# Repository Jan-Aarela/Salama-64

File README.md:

<!-- vim: ft=markdown nospell
-->
<i>

# Selkäsalama-64
Möykkäwaunujen proto salaman teon aikana huomasin, että salaman koko oli pikkasen pienempi mitä kuvittelin. Täysin toimiva siitähän tuli ja varsin hieno vaikka nopeasti tekasin sen.

Kaytin protoversiota yövalona kotona :D ja iski idea. Mitä jos, tästä tekisi selkäsalaman.  
[Niinkuin ysärillä...](https://github.com/Elektroniikkakerho/Archived-projects/tree/master/salama)  KiCadi tulille vaan ja lopputulos alla:

## Kuvia härpäkkeestä
|Homma in action|Etupuoli|Takapuoli| Takapuoli Kuorilla|
|---|---|---|---|
| | |  | 

## Skema
Homma toimii siten, että virtapankista tulee 5V ja menee suoraan piiriin. Konkka tasoittaa virran ja vastus toimii kuormana, mikäli virtapankki sammuu liian vähäistä virrankulutuksesta. Toinen ja energia tehokkaampi vaihtoehto on käyttää virtapankki kikkaa, eli ajoittain piikittää virran kulutusta ohjaamalla transistorin avulla vastusta.

Ledit on jaettu puolin kahteen eri charlieplexiin. (7^2-7 (-10) viritelmällä).  
Miksei kaikkia ledejä yhteen pleksiin? No siksi koska jos yhteen pleksiin laittaa kaikki ledit niin duty cycle olisi ~1.5%, joka on aika pieni. Kahdella pleksillä sen saa ~3%, jolloin ledit ovat kirkkaampia.

Napin tai liukukytkimen voi halutessa laittaa SW1 kohtaan johdoilla ja laittaa itse napin/liukukytkimen haalareihin, esim. kaulapantaan tai mikälie sen oikea nimi onkaan.

## Osaluettelo
| KPL | MITÄ               | HUOM    | 
|:---:|:---                |:---    |
|  1  | ATtiny 861A SOIC   |       Vähintään: Flash 4KB -  SRAM 256B   |
|  64 | 5mm DIP LED        | Tekijällä XL-502UBC ledit  |
|  14  | 27 Ohm 1206        |    < 20ma per IO pin    |
|  1  | 10 uF tant. 2312 SMD     |    Virtalähteen virran tasoitusta varten |
|  8  | Johdon pätkiä    |    Levyjen yhdistämiseen AWG 22-24 |
| 1 | Virtakaapelipari | Esim. USB |
| 1 | 6 pinninen rima | THT vaaka versio |

| Muuta?  |
|:---|
| Fläshäykseen Arduino ja 6 pinninen rima |
| PETG Filamettia kuorien tulostamiseen|
| (Optinal) Lisävastus mikäli salama sammuu|
| (Optinal) 2kpl 1206 100 nF keraamisia konkkia  |
| (Optinal) Nappi/Liukukytkin halutessa ja siihen johdot|

## Piirilevyt

Mikäli kerholla ei ole levyjä tähän projektiin, voit yrittää tehdä levyn esimerkiksi jyrsimällä tai etsaamalla. Tracien paksuudet ovat 0.4mm kestävyyden/tuotannon tolaranssin takia. Projektiin käy esimerkiksi 2-puoleinen 1oz 1.6mm PCB. Jos teet paksummasta levystä piirilevyt, joudut muokkaamaan kuorien mitat, jotta levyt mahtuvat niihin. 

Läpivientien kanssa joutuu painimaan sillä jyrsimisen/perus etsauksen jälkeen ne ei ilmesty itsestään vaan ne joutuu manuaalisesti tehdä ne. Yks tapa on käyttää läpivientiniittejä ja pressiä. Pressin jälkeen kannattaa ehdottamasti juottaa niitit traceihin, että varmasti toimivat. Jos niitit eivät mahdu reikiin, täytyy vaihtaa vioiden ja ledien reikien koot kicadillä. Tarkista, että niittien läpi mahtuu komponentit. Voi olla, että reikiä pitää kasvattaa...

## LEDIT
Tähän kannatta käyttää hyvin kirkkaita ledejä esim.  10000 mcd tai kirkkaammat,   
koska yhden ledin duty cycle on sen 1/32 ajasta eli ~ 3%.

Testaa ledin kirkkaus virtalähteellä.
Asetukset: square, 2.5V offset, 2.5V amplitude ja 3% duty cycle.

**Jos ledejä ei ole diffusoitu, niin ehdottamasti diffusoi ne.**  
Muuten selkäsalamasta tulee saatananmoinen valokeila ja sivusta katsottuna näyttää himmeältä.  

Hidas, mutta puhtaamman jäljen saat kun hiot jokaisen ledin 400-600 grid vesihiomapaperilla.

Toinen ja huomattavasti nopeampi tapa on käyttää hiekkapuhallinta. 
Eli laita kaikki ledit reikälevyyn ja teippaa ledien jalat.
Samaan tyliin kuin konkat tulee rullana. Ja ei muutakun hiekkapuhaltimella ammuskelemaan.
Voit puhdistaa ledit hiekasta laittamalla ledit astiaan jossa on nestettä (vesi/ipa) ja astian ultraäänipuhdistimeen.

## Kasausohjeet
Projekti aika pitkälti noudattaa possusalaman ohjeita.

 1. Juota siis piiri, konkka, 14 vastusta ja piikkirima.  
    Piikkirimasta trimmataan 4 sisimmäistä jalkaa, että se asettuisi lättänä.

2. Seuraavaksi laitetaan piirilevyt kiinni haalareihin.  
    Katko ledien jalat teräviksi ja yritä kohdistaa levy paikalleen.  
    Tässä kannattaa laittaa ledit niin, että haalarin salaman ääriviivat kulkee ledien keskellä.  
    Ledit mahdollisman hyvin kiinni piirilevyä vasten, näyttää suoremmalta.  
    Ja kannattaa jättää pieni rako piirilevyjen välille,  ettei hankaudu.  
    Tee sama toiselle piirilevylle. 

3. Sitten voit juottaa hyppyjohdot levylle, jossa on piiri.  
    Kannattaa juottaa hyvin ja niin että johdon muovi on mahdollisimman lähellä levyä.  
    Katko juottamisen jälkeen etupuolelta töpröttävät johdot pätkät.

4. Sittenkun kummatkin levyt ovat haalareissa kiinni, yhdistä levyt hyppykaapelilla.  
    Kaapelit menee järjestyksessä. Kanattaa olla vähän löysää, että koko härpäke pystyy taittumaan.

5. Kiinnitä Ardu piikkirimaan kiinni ja siirrä koodi levylle käyttäen AVR-ISP.  
    Ohjeet alempana.

6.  Jos kaikki toimii, juota seuraavaksi virtakaapeli ja tarvittaessa kuormavastus mikäli virtapankki lopettaa virranannon (virtasyöppö esto). Esim. 110 Ohm tai 169 Ohm...

7. Kuoret saa tulostettua FabLabilla ja mielellään kannattaa käyttää PETG. Tämä taipuu hyvin eikä halkea yhtä herkästi verrattuna esim. ABS muoviin. Tulostuksen jälkeen pitää putsata kuorien klipsien/kielien supportit pois. Esim varovasti veitsellä. Voit testata, että mahtuuko levy siihen, jos laitat 1.6mm levyn pätkän klipsin ja reunan (jossa piirilevyt istuu) väliin.

    Jos olet tehnyt piirilevyt paksummasta levystä, pitää muokata kuorien mittoja joko muokkaamalla STL tai blender projekti tiedostoa. 

8. Kuoret sopivat kummallekin piirilevylle.  
    Kolvilla voit tehdä master levyn kuoren reunalle reiän virtakaapelille.

    Kannattaa laittaa kuoret kiinni siten, että laitat ensin terävän kulman ensin kiinni ja siitä sitten siirry ylöspäin. Venytä kuorta ulospäin paina kiinni.

    Juuh, eikait siinä. Nyt **JÖÖTI** "possu" selässä  👌

## Koodi

```bash
# Siirry koodi kansioon
cd src/

# Koodin kääntäminen
avr-gcc -mmcu=attiny861 main.c kuviot.c vilkutus_charlie.c -I./ -Os -ffunction-sections -fdata-sections -Wl,--gc-sections -DF_CPU=8000000U

# Fuse asetukset
avrdude -c avrisp -p t861 -P /dev/ttyUSB0 -b 19200 -U lfuse:w:0xe2:m -U hfuse:w:0xdf:m

# Koodin siirto levylle
avrdude -c avrisp -p t861 -P /dev/ttyUSB0 -b 19200 -U flash:w:a.out

# Testaukseen voit käyttää yhtä komento riviä yhdistämällä koodin käännös ja siirto komennot (bash:)
avr-gcc -mmcu=attiny861 main.c kuviot.c vilkutus_charlie.c -I./ -Os -ffunction-sections -fdata-sections -Wl,--gc-sections -DF_CPU=8000000U && sudo avrdude -c avrisp -p t861 -P /dev/ttyUSB0 -b 19200 -U flash:w:a.out
```

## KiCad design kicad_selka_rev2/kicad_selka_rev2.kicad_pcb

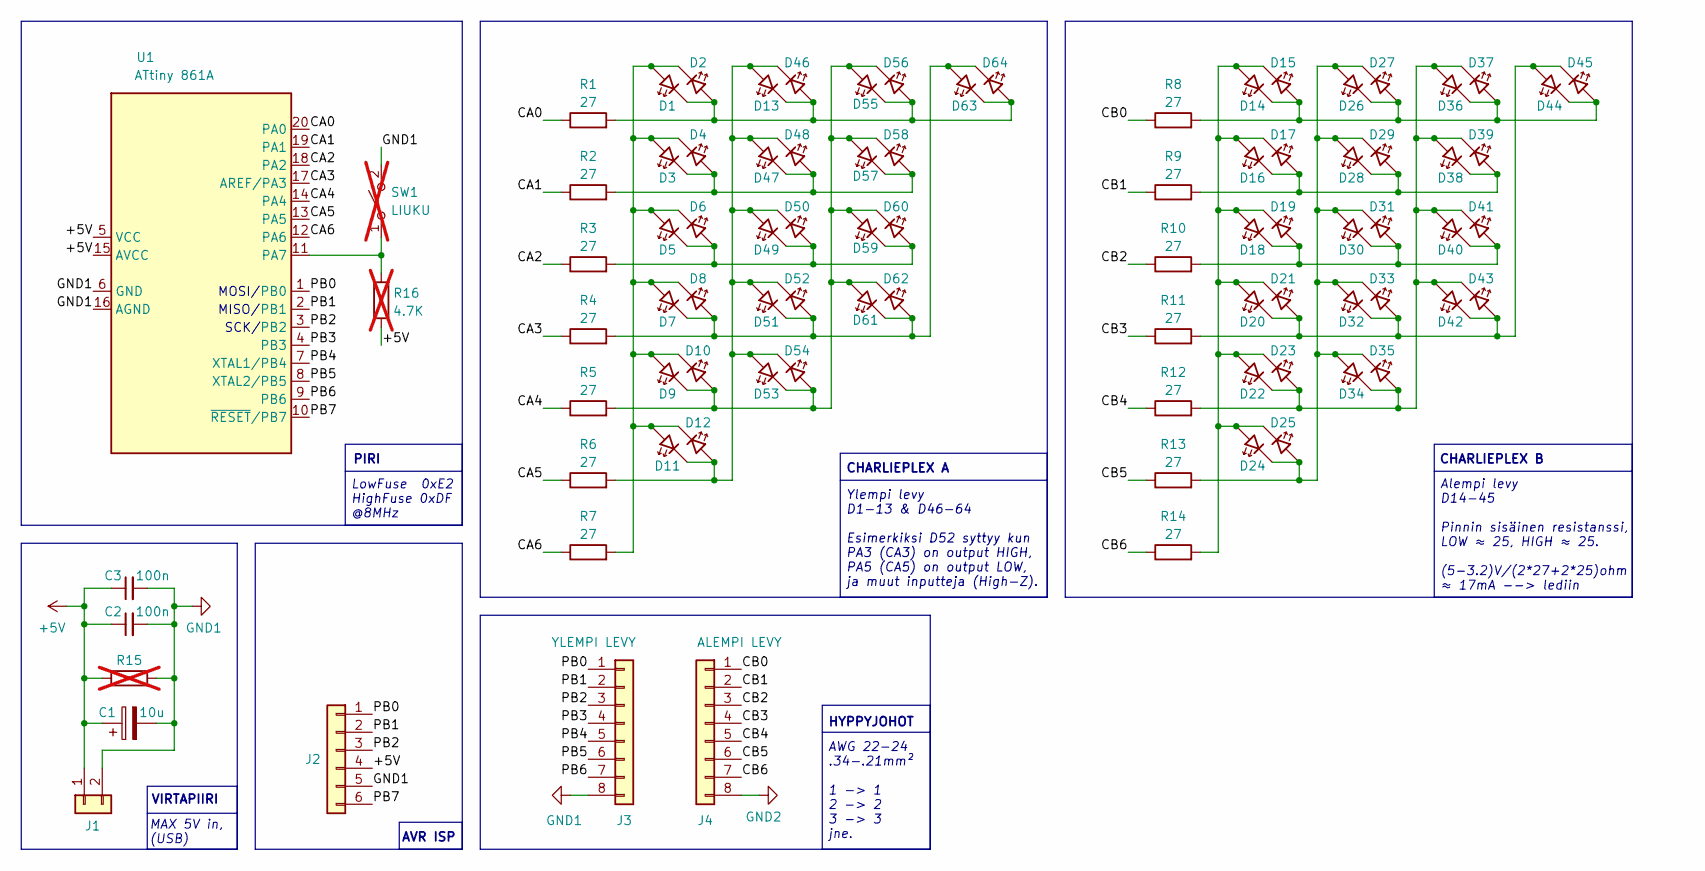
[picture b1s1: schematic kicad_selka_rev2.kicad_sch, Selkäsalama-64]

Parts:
C1: 10u; CP_EIA-6032-28_Kemet-C_HandSolder
C2, C3: 100n; C_1206_3216Metric_Pad1.33x1.80mm_HandSolder
D1, D2, D3, D4, D5, D6, D7, D8, D9, D10, D11, D12, D13, D14, D15, D16, D17, D18, D19, D20, D21, D22, D23, D24, D25, D26, D27, D28, D29, D30, D31, D32, D33, D34, D35, D36, D37, D38, D39, D40, D41, D42, D43, D44, D45, D46, D47, D48, D49, D50, D51, D52, D53, D54, D55, D56, D57, D58, D59, D60, D61, D62, D63, D64: LED_45deg; LED_D5.0mm_blue_zani
J1: Conn_01x02; PinHeader_1x02_P2.54mm_Vertical
J2: Conn_01x06; PinHeader_1x06_P2.54mm_Horizontal_smd_tht
J3, J4: Conn_01x08; PinHeader_1x08_P2.00mm_Vertical_levee
R1, R2, R3, R4, R5, R6, R7, R8, R9, R10, R11, R12, R13, R14: 27; R_1206_3216Metric_Pad1.30x1.75mm_HandSolder
R15: X; R_1210_3225Metric_Pad1.30x2.65mm_HandSolder; not fitted
R16: 4.7K; R_0805_2012Metric_Pad1.20x1.40mm_HandSolder; not fitted
SW1: LIUKU; PinHeader_1x02_P2.54mm_Vertical; not fitted
U1: ATtiny 861A; SOIC-20W_7.5x12.8mm_P1.27mm

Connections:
+5V: C1.1, C2.1, C3.1, J1.1, J2.4, R15.1, R16.1, U1.5 (VCC), U1.15 (AVCC)
/CA0: R1.1, U1.20 (PA0)
/CA1: R2.1, U1.19 (PA1)
/CA2: R3.1, U1.18 (PA2)
/CA3: R4.1, U1.17 (AREF/PA3)
/CA4: R5.1, U1.14 (PA4)
/CA5: R6.1, U1.13 (PA5)
/CA6: R7.1, U1.12 (PA6)
/CB0: J4.1, R8.1
/CB1: J4.2, R9.1
/CB2: J4.3, R10.1
/CB3: J4.4, R11.1
/CB4: J4.5, R12.1
/CB5: J4.6, R13.1
/CB6: J4.7, R14.1
/PB0: J2.1, J3.1, U1.1 (PB0)
/PB1: J2.2, J3.2, U1.2 (PB1)
/PB2: J2.3, J3.3, U1.3 (PB2)
/PB3: J3.4, U1.4 (PB3)
/PB4: J3.5, U1.7 (XTAL1/PB4)
/PB5: J3.6, U1.8 (XTAL2/PB5)
/PB6: J3.7, U1.9 (PB6)
/PB7: J2.6, U1.10 (~RESET/PB7)
GND1: C1.2, C2.2, C3.2, J1.2, J2.5, J3.8, R15.2, SW1.2 (B), U1.6 (GND), U1.16 (AGND)
GND2: J4.8
unnamed: D1.2 (A), D2.1 (K), D3.2 (A), D4.1 (K), D5.2 (A), D6.1 (K), D7.2 (A), D8.1 (K), D9.2 (A), D10.1 (K), D11.2 (A), D12.1 (K), R7.2
unnamed: D1.1 (K), D2.2 (A), D13.1 (K), D46.2 (A), D55.1 (K), D56.2 (A), D63.1 (K), D64.2 (A), R1.2
unnamed: D3.1 (K), D4.2 (A), D47.1 (K), D48.2 (A), D57.1 (K), D58.2 (A), R2.2
unnamed: D9.1 (K), D10.2 (A), D53.1 (K), D54.2 (A), D55.2 (A), D56.1 (K), D57.2 (A), D58.1 (K), D59.2 (A), D60.1 (K), D61.2 (A), D62.1 (K), R5.2
unnamed: D11.1 (K), D12.2 (A), D13.2 (A), D46.1 (K), D47.2 (A), D48.1 (K), D49.2 (A), D50.1 (K), D51.2 (A), D52.1 (K), D53.2 (A), D54.1 (K), R6.2
unnamed: D14.2 (A), D15.1 (K), D16.2 (A), D17.1 (K), D18.2 (A), D19.1 (K), D20.2 (A), D21.1 (K), D22.2 (A), D23.1 (K), D24.2 (A), D25.1 (K), R14.2
unnamed: D14.1 (K), D15.2 (A), D26.1 (K), D27.2 (A), D36.1 (K), D37.2 (A), D44.1 (K), D45.2 (A), R8.2
unnamed: D16.1 (K), D17.2 (A), D28.1 (K), D29.2 (A), D38.1 (K), D39.2 (A), R9.2
unnamed: D18.1 (K), D19.2 (A), D30.1 (K), D31.2 (A), D40.1 (K), D41.2 (A), R10.2
unnamed: D20.1 (K), D21.2 (A), D32.1 (K), D33.2 (A), D42.1 (K), D43.2 (A), D44.2 (A), D45.1 (K), R11.2
unnamed: D22.1 (K), D23.2 (A), D34.1 (K), D35.2 (A), D36.2 (A), D37.1 (K), D38.2 (A), D39.1 (K), D40.2 (A), D41.1 (K), D42.2 (A), D43.1 (K), R12.2
unnamed: D24.1 (K), D25.2 (A), D26.2 (A), D27.1 (K), D28.2 (A), D29.1 (K), D30.2 (A), D31.1 (K), D32.2 (A), D33.1 (K), D34.2 (A), D35.1 (K), R13.2
unnamed: D5.1 (K), D6.2 (A), D49.1 (K), D50.2 (A), D59.1 (K), D60.2 (A), R3.2
unnamed: D7.1 (K), D8.2 (A), D51.1 (K), D52.2 (A), D61.1 (K), D62.2 (A), D63.2 (A), D64.1 (K), R4.2
unnamed: R16.2, SW1.1 (A), U1.11 (PA7)

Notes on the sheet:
VIRTAPIIRI
SCK/
MISO/
MOSI/
AWG 22-24 .34-.21mm² 1 -> 1 2 -> 2 3 -> 3 jne.
CHARLIEPLEX A
CHARLIEPLEX B
MAX 5V in, (USB)
Ylempi levy D1-13 & D46-64 Esimerkiksi D52 syttyy kun PA3 (CA3) on output HIGH, PA5 (CA5) on output LOW, ja muut inputteja (High-Z).
Alempi levy D14-45 Pinnin sisäinen resistanssi, LOW ≈ 25, HIGH ≈ 25. (5-3.2)V/(2*27+2*25)ohm ≈ 17mA --> lediin
AVR ISP
PIRI
LowFuse 0xE2 HighFuse 0xDF @8MHz
HYPPYJOHOT

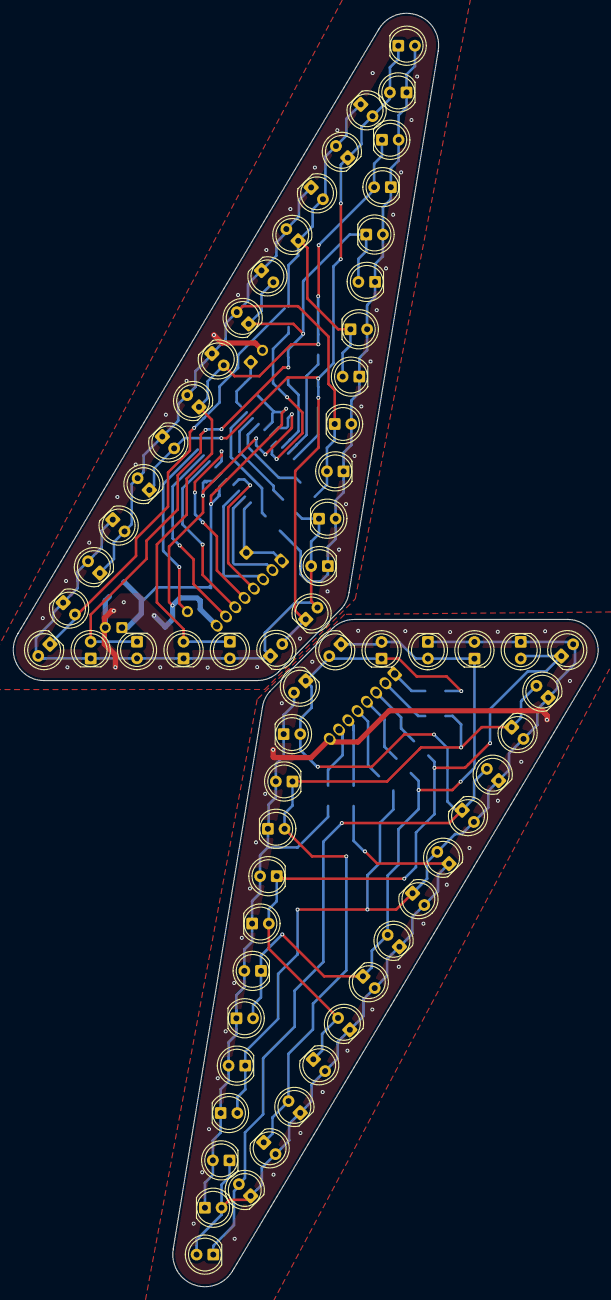
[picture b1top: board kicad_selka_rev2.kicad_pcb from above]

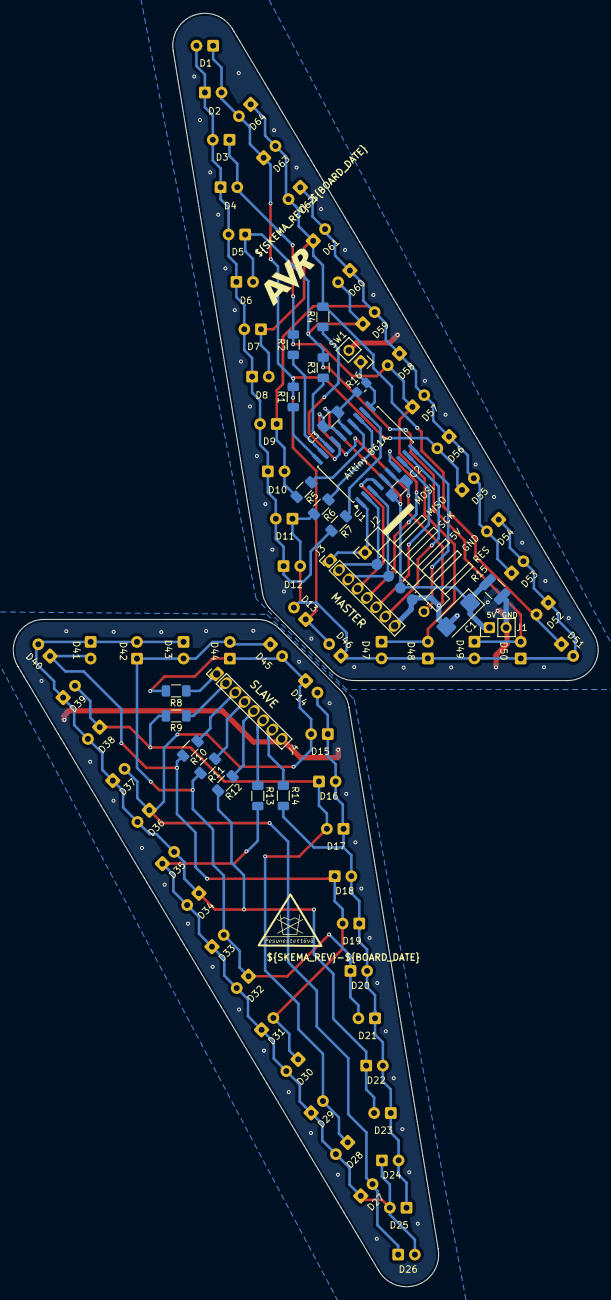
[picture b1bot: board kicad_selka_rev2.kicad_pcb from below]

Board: 2 copper layers, 89.2 x 194.1 mm, 89 parts (25 on the bottom side), 39 nets.

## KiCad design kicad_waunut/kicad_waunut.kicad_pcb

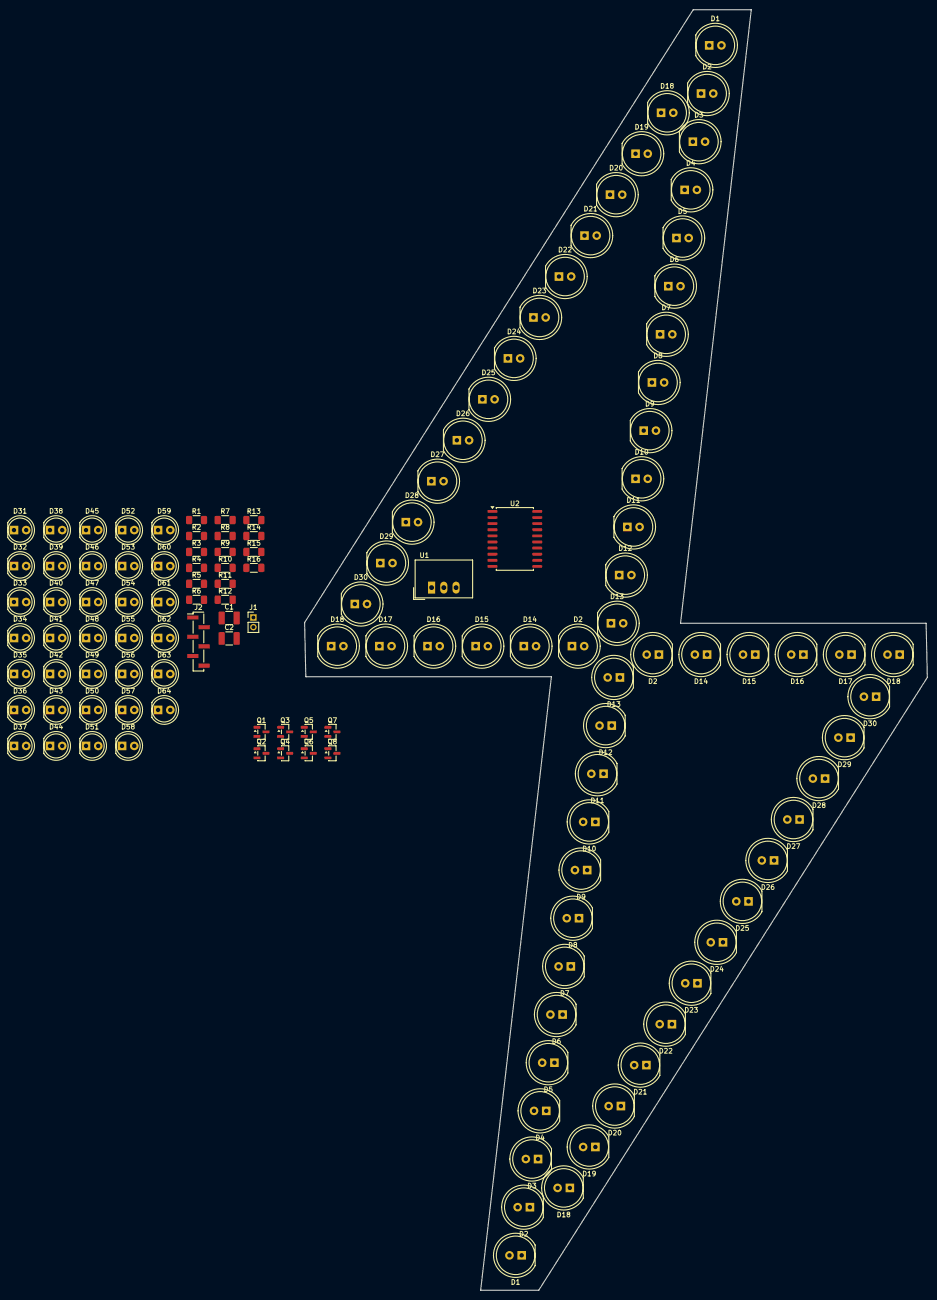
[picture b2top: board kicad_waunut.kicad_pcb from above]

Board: 2 copper layers, 129.3 x 265.9 mm, 128 parts (0 on the bottom side), 43 nets, no tracks yet.

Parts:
C1, C2: 10 u; C_1210_3225Metric_Pad1.33x2.70mm_HandSolder
D1, D1#2, D2, D2#2, D2#3, D2#4, D3, D3#2, D4, D4#2, D5, D5#2, D6, D6#2, D7, D7#2, D8, D8#2, D9, D9#2, D10, D10#2, D11, D11#2, D12, D12#2, D13, D13#2, D14, D14#2, D15, D15#2, D16, D16#2, D17, D17#2, D18, D18#2, D18#3, D18#4, D19, D19#2, D20, D20#2, D21, D21#2, D22, D22#2, D23, D23#2, D24, D24#2, D25, D25#2, D26, D26#2, D27, D27#2, D28, D28#2, D29, D29#2, D30, D30#2: LED; LED_D8.0mm
D31, D32, D33, D34, D35, D36, D37, D38, D39, D40, D41, D42, D43, D44, D45, D46, D47, D48, D49, D50, D51, D52, D53, D54, D55, D56, D57, D58, D59, D60, D61, D62, D63, D64: LED; LED_D5.0mm
J1: Conn_01x02_Pin; PinHeader_1x02_P2.00mm_Vertical
J2: Conn_01x06_Pin; PinHeader_1x06_P2.00mm_Vertical_SMD_Pin1Left
Q1, Q2, Q3, Q4, Q5, Q6, Q7, Q8: NPN; SOT-23
R1, R2, R3, R4, R5, R6, R7, R8: 110; R_1206_3216Metric_Pad1.30x1.75mm_HandSolder
R9, R10, R11, R12, R13, R14, R15, R16: 1000; R_1206_3216Metric_Pad1.30x1.75mm_HandSolder
U1: TSR1-2450E; Converter_DCDC_TRACO_TSR-1_THT
U2: ATtiny861A-S; SOIC-20W_7.5x12.8mm_P1.27mm

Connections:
+5V: C1.1, J2.4, U1.3 (Vout), U2.5 (VCC), U2.15 (AVCC)
+12V: C2.1, J1.1, U1.1 (Vin)
GND: C1.2, C2.2, J1.2, J2.5, Q1.3 (E), Q2.3 (E), Q3.3 (E), Q4.3 (E), Q5.3 (E), Q6.3 (E), Q7.3 (E), Q8.3 (E), U1.2 (GND), U2.6 (GND), U2.16 (AGND)
unnamed: D1.2 (A), D1#2.2 (A), D9.2 (A), D9#2.2 (A), D17.2 (A), D17#2.2 (A), D25.2 (A), D25#2.2 (A), D33.2 (A), D41.2 (A), D49.2 (A), D57.2 (A), R1.2
unnamed: D1.1 (K), D1#2.1 (K), D2.1 (K), D2#2.1 (K), D2#3.1 (K), D2#4.1 (K), D3.1 (K), D3#2.1 (K), D4.1 (K), D4#2.1 (K), D5.1 (K), D5#2.1 (K), D6.1 (K), D6#2.1 (K), D7.1 (K), D7#2.1 (K), D8.1 (K), D8#2.1 (K), Q1.1 (C)
unnamed: D2.2 (A), D2#2.2 (A), D2#3.2 (A), D2#4.2 (A), D10.2 (A), D10#2.2 (A), D18.2 (A), D18#2.2 (A), D18#3.2 (A), D18#4.2 (A), D26.2 (A), D26#2.2 (A), D34.2 (A), D42.2 (A), D50.2 (A), D58.2 (A), R2.2
unnamed: D9.1 (K), D9#2.1 (K), D10.1 (K), D10#2.1 (K), D11.1 (K), D11#2.1 (K), D12.1 (K), D12#2.1 (K), D13.1 (K), D13#2.1 (K), D14.1 (K), D14#2.1 (K), D15.1 (K), D15#2.1 (K), D16.1 (K), D16#2.1 (K), Q2.1 (C)
unnamed: D3.2 (A), D3#2.2 (A), D11.2 (A), D11#2.2 (A), D19.2 (A), D19#2.2 (A), D27.2 (A), D27#2.2 (A), D35.2 (A), D43.2 (A), D51.2 (A), D59.2 (A), R3.2
unnamed: D4.2 (A), D4#2.2 (A), D12.2 (A), D12#2.2 (A), D20.2 (A), D20#2.2 (A), D28.2 (A), D28#2.2 (A), D36.2 (A), D44.2 (A), D52.2 (A), D60.2 (A), R4.2
unnamed: D5.2 (A), D5#2.2 (A), D13.2 (A), D13#2.2 (A), D21.2 (A), D21#2.2 (A), D29.2 (A), D29#2.2 (A), D37.2 (A), D45.2 (A), D53.2 (A), D61.2 (A), R5.2
unnamed: D6.2 (A), D6#2.2 (A), D14.2 (A), D14#2.2 (A), D22.2 (A), D22#2.2 (A), D30.2 (A), D30#2.2 (A), D38.2 (A), D46.2 (A), D54.2 (A), D62.2 (A), R6.2
unnamed: D7.2 (A), D7#2.2 (A), D15.2 (A), D15#2.2 (A), D23.2 (A), D23#2.2 (A), D31.2 (A), D39.2 (A), D47.2 (A), D55.2 (A), D63.2 (A), R7.2
unnamed: D8.2 (A), D8#2.2 (A), D16.2 (A), D16#2.2 (A), D24.2 (A), D24#2.2 (A), D32.2 (A), D40.2 (A), D48.2 (A), D56.2 (A), D64.2 (A), R8.2
unnamed: D17.1 (K), D17#2.1 (K), D18.1 (K), D18#2.1 (K), D18#3.1 (K), D18#4.1 (K), D19.1 (K), D19#2.1 (K), D20.1 (K), D20#2.1 (K), D21.1 (K), D21#2.1 (K), D22.1 (K), D22#2.1 (K), D23.1 (K), D23#2.1 (K), D24.1 (K), D24#2.1 (K), Q3.1 (C)
unnamed: D25.1 (K), D25#2.1 (K), D26.1 (K), D26#2.1 (K), D27.1 (K), D27#2.1 (K), D28.1 (K), D28#2.1 (K), D29.1 (K), D29#2.1 (K), D30.1 (K), D30#2.1 (K), D31.1 (K), D32.1 (K), Q4.1 (C)
unnamed: D33.1 (K), D34.1 (K), D35.1 (K), D36.1 (K), D37.1 (K), D38.1 (K), D39.1 (K), D40.1 (K), Q5.1 (C)
unnamed: D41.1 (K), D42.1 (K), D43.1 (K), D44.1 (K), D45.1 (K), D46.1 (K), D47.1 (K), D48.1 (K), Q6.1 (C)
unnamed: D49.1 (K), D50.1 (K), D51.1 (K), D52.1 (K), D53.1 (K), D54.1 (K), D55.1 (K), D56.1 (K), Q7.1 (C)
unnamed: D57.1 (K), D58.1 (K), D59.1 (K), D60.1 (K), D61.1 (K), D62.1 (K), D63.1 (K), D64.1 (K), Q8.1 (C)
unnamed: J2.1, R9.1, U2.1 (PB0)
unnamed: J2.2, R10.1, U2.2 (PB1)
unnamed: J2.3, R11.1, U2.3 (PB2)
unnamed: J2.6, R16.1, U2.10 (~RESET/PB7)
unnamed: Q1.2 (B), R9.2
unnamed: Q2.2 (B), R10.2
unnamed: Q3.2 (B), R11.2
unnamed: Q4.2 (B), R12.2
unnamed: Q5.2 (B), R13.2
unnamed: Q6.2 (B), R14.2
unnamed: Q7.2 (B), R15.2
unnamed: Q8.2 (B), R16.2
unnamed: R4.1, U2.17 (AREF/PA3)
unnamed: R1.1, U2.20 (PA0)
unnamed: R2.1, U2.19 (PA1)
unnamed: R3.1, U2.18 (PA2)
unnamed: R5.1, U2.14 (PA4)
unnamed: R6.1, U2.13 (PA5)
unnamed: R7.1, U2.12 (PA6)
unnamed: R8.1, U2.11 (PA7)
unnamed: R12.1, U2.4 (PB3)
unnamed: R15.1, U2.9 (PB6)
unnamed: R13.1, U2.7 (XTAL1/PB4)
unnamed: R14.1, U2.8 (XTAL2/PB5)

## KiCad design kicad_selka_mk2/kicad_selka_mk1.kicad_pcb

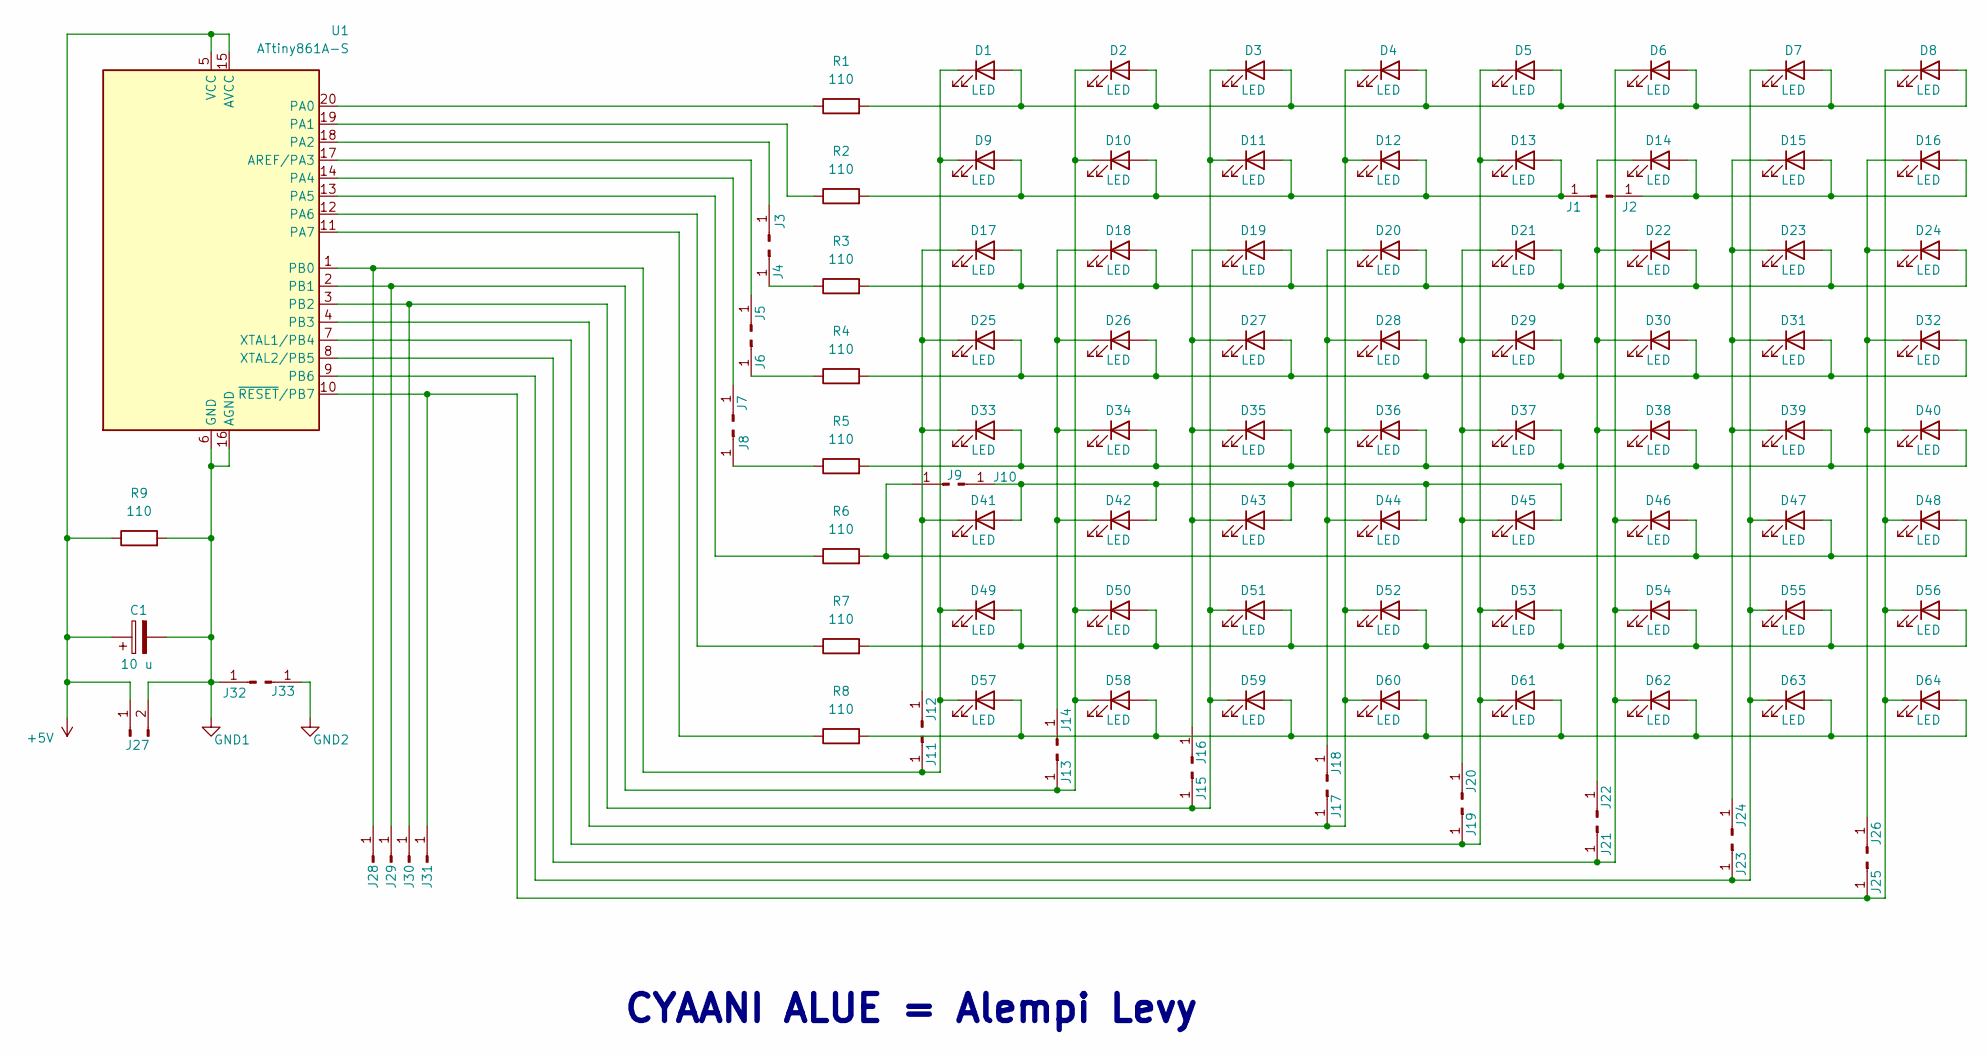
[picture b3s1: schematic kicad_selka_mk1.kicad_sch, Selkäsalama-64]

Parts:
C1: 10 u; C_1210_3225Metric_Pad1.33x2.70mm_HandSolder
D1, D2, D3, D4, D5, D6, D7, D8, D9, D10, D11, D12, D13, D14, D15, D16, D17, D18, D19, D20, D21, D22, D23, D24, D25, D26, D27, D28, D29, D30, D31, D32, D33, D34, D35, D36, D37, D38, D39, D40, D41, D42, D43, D44, D45, D46, D47, D48, D49, D50, D51, D52, D53, D54, D55, D56, D57, D58, D59, D60, D61, D62, D63, D64: LED; LED_D5.0mm
J1, J2, J3, J5, J6, J7, J8, J9, J10, J11, J12, J13, J14, J15, J16, J17, J18, J19, J20, J21, J22, J23, J24, J25, J26, J32, J33: Conn_01x01_Pin; PinSocket_1x01_P2.54mm_Vertical
J4: Conn_01x01_Pin; Pin_D0.7mm_L6.5mm_W1.8mm_FlatFork
J27: Conn_01x02_Pin; PinHeader_1x02_P2.00mm_Vertical
J28, J29, J30, J31: Conn_01x01_Pin; TestPoint_Pad_1.0x1.0mm
R1, R2, R3, R4, R5, R6, R7, R8, R9: 110; R_1206_3216Metric_Pad1.30x1.75mm_HandSolder
U1: ATtiny861A-S; SOIC-20W_7.5x12.8mm_P1.27mm

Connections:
+5V: C1.1, J27.1, R9.1, U1.5 (VCC), U1.15 (AVCC)
GND1: C1.2, J27.2, J32.1, R9.2, U1.6 (GND), U1.16 (AGND)
GND2: J33.1
unnamed: D1.2 (A), D2.2 (A), D3.2 (A), D4.2 (A), D5.2 (A), D6.2 (A), D7.2 (A), D8.2 (A), R1.2
unnamed: D1.1 (K), D9.1 (K), D49.1 (K), D57.1 (K), J11.1, J28.1, U1.1 (PB0)
unnamed: D9.2 (A), D10.2 (A), D11.2 (A), D12.2 (A), D13.2 (A), J1.1, R2.2
unnamed: D2.1 (K), D10.1 (K), D50.1 (K), D58.1 (K), J13.1, J29.1, U1.2 (PB1)
unnamed: D3.1 (K), D11.1 (K), D51.1 (K), D59.1 (K), J15.1, J30.1, U1.3 (PB2)
unnamed: D4.1 (K), D12.1 (K), D52.1 (K), D60.1 (K), J17.1, U1.4 (PB3)
unnamed: D5.1 (K), D13.1 (K), D53.1 (K), D61.1 (K), J19.1, U1.7 (XTAL1/PB4)
unnamed: D14.2 (A), D15.2 (A), D16.2 (A), J2.1
unnamed: D14.1 (K), D22.1 (K), D30.1 (K), D38.1 (K), J22.1
unnamed: D15.1 (K), D23.1 (K), D31.1 (K), D39.1 (K), J24.1
unnamed: D16.1 (K), D24.1 (K), D32.1 (K), D40.1 (K), J26.1
unnamed: D17.2 (A), D18.2 (A), D19.2 (A), D20.2 (A), D21.2 (A), D22.2 (A), D23.2 (A), D24.2 (A), R3.2
unnamed: D17.1 (K), D25.1 (K), D33.1 (K), D41.1 (K), J12.1
unnamed: D18.1 (K), D26.1 (K), D34.1 (K), D42.1 (K), J14.1
unnamed: D19.1 (K), D27.1 (K), D35.1 (K), D43.1 (K), J16.1
unnamed: D20.1 (K), D28.1 (K), D36.1 (K), D44.1 (K), J18.1
unnamed: D21.1 (K), D29.1 (K), D37.1 (K), D45.1 (K), J20.1
unnamed: D25.2 (A), D26.2 (A), D27.2 (A), D28.2 (A), D29.2 (A), D30.2 (A), D31.2 (A), D32.2 (A), R4.2
unnamed: D33.2 (A), D34.2 (A), D35.2 (A), D36.2 (A), D37.2 (A), D38.2 (A), D39.2 (A), D40.2 (A), R5.2
unnamed: D41.2 (A), D42.2 (A), D43.2 (A), D44.2 (A), D45.2 (A), J10.1
unnamed: D46.2 (A), D47.2 (A), D48.2 (A), J9.1, R6.2
unnamed: D6.1 (K), D46.1 (K), D54.1 (K), D62.1 (K), J21.1, U1.8 (XTAL2/PB5)
unnamed: D7.1 (K), D47.1 (K), D55.1 (K), D63.1 (K), J23.1, U1.9 (PB6)
unnamed: D8.1 (K), D48.1 (K), D56.1 (K), D64.1 (K), J25.1, J31.1, U1.10 (~RESET/PB7)
unnamed: D49.2 (A), D50.2 (A), D51.2 (A), D52.2 (A), D53.2 (A), D54.2 (A), D55.2 (A), D56.2 (A), R7.2
unnamed: D57.2 (A), D58.2 (A), D59.2 (A), D60.2 (A), D61.2 (A), D62.2 (A), D63.2 (A), D64.2 (A), R8.2
unnamed: J3.1, U1.18 (PA2)
unnamed: J4.1, R3.1
unnamed: J5.1, U1.17 (AREF/PA3)
unnamed: J6.1, R4.1
unnamed: J7.1, U1.14 (PA4)
unnamed: J8.1, R5.1
unnamed: R1.1, U1.20 (PA0)
unnamed: R2.1, U1.19 (PA1)
unnamed: R6.1, U1.13 (PA5)
unnamed: R7.1, U1.12 (PA6)
unnamed: R8.1, U1.11 (PA7)

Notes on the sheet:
CYAANI ALUE = Alempi Levy

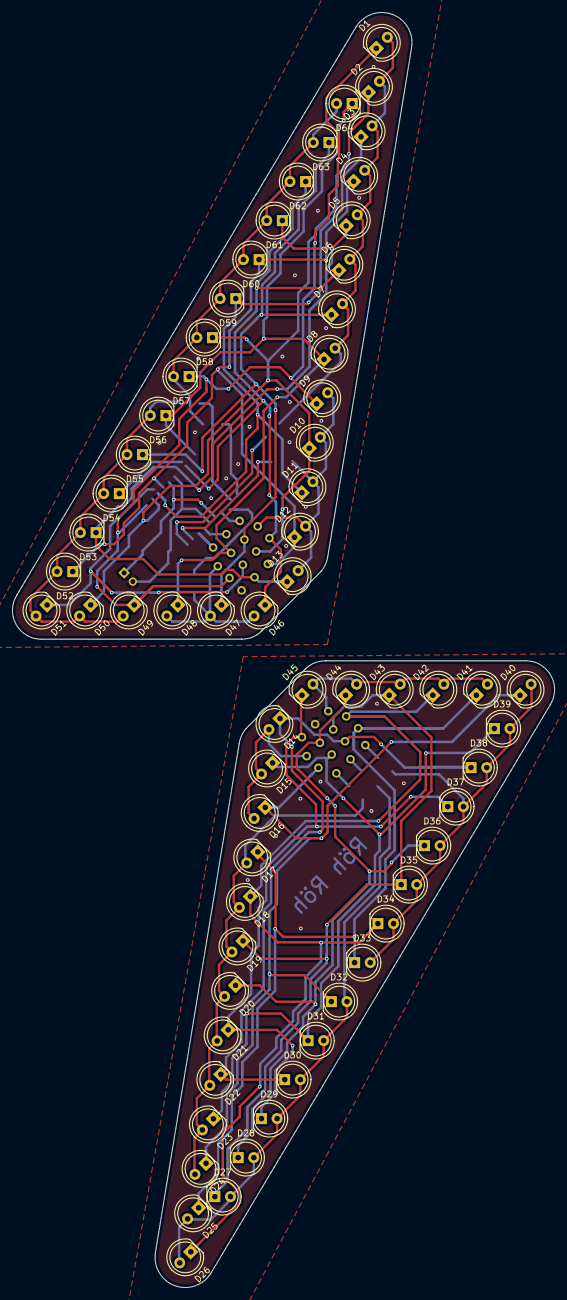
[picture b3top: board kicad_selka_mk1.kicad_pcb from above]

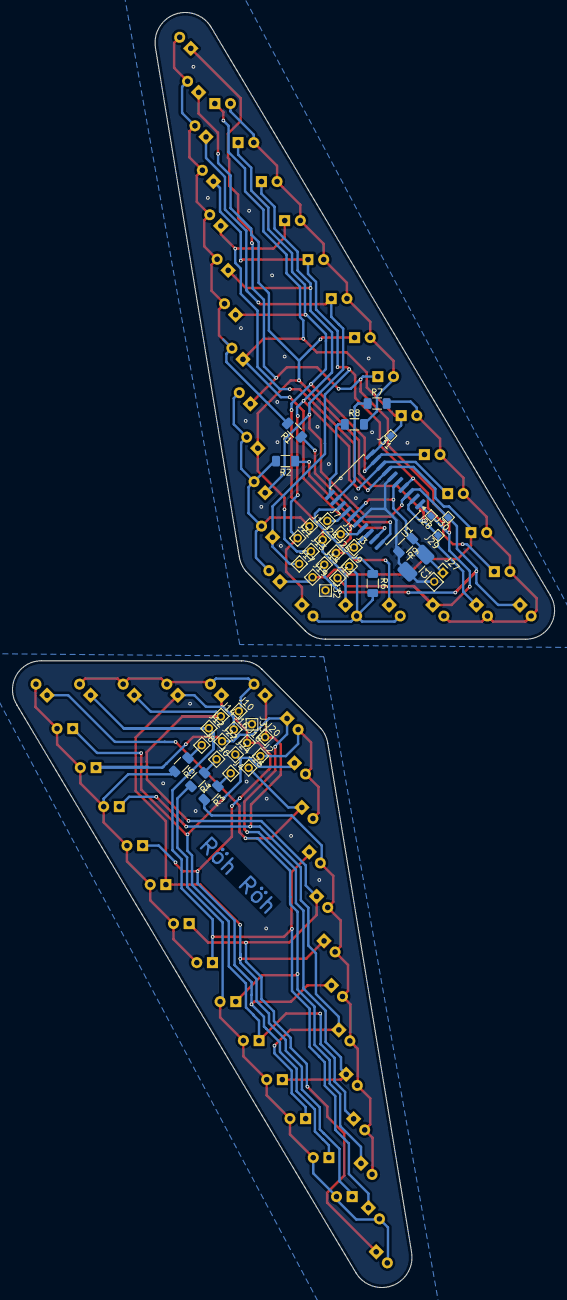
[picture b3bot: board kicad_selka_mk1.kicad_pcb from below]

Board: 2 copper layers, 88.0 x 206.9 mm, 108 parts (44 on the bottom side), 39 nets.

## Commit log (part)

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2026-02-06 Uusi leiska
2026-02-12 Ny ois eka toimiva levy
2026-02-12 Init Next Gen Selkäsalama
2026-02-13 Ahasta
2026-02-13 Selkäsalaman skemaan lisätty jumperit
2026-02-13 Selkäsalama 90% done
2026-02-14 Selkäsalama 95% done
2026-02-15 Selkäsalama redo
    1 ledi meni väärälle puolelle -> 31 & 33 lediä :C
    Samahan se oli tehdä koko leiska uudelleen parammilla array
    ledipaikoilla...
2026-02-15 selkäsalama mk1 done
2026-02-21 selkäsalama mk1 rev 2
2026-03-01 Selkäsalama toimii
    Kasattu selkäsalama ja se toimii.
    Ledien PWM ajotuksia puolittu, oli 312us eli 64 ledillä se olisi ollut
    50Hz. Nyt 156 jolloin tajuus on sen 100Hz verran.
    Korjattu muutama efekti.
2026-03-03 Efektien tuunausta
    Korjattu efekteja ja lisätty
    vilkutus.c yksinkertaistettu.
2026-03-06 Init waunut salama
2026-03-09 2 lediä vilkkuu - vilkutus_2x.c
    Jostain syystä kummallinen if statementti jossa 2 lediä palaa mutta eri
    kirrkaudella.
    Muutama ledi himmenee/kirkastuu. hmm...
    Muuten jeba
2026-03-11 Selkäsalaman kuoret
    blender_selka kansiosta nyt löytyy selkäsalmaan kuoret.
    blender tiedostossa itse levy ja iteraatioita kuoreja.
    V3 on hjuva ja napsahtaa mukavasti kohdalleen.
    Valmiina kuoret_v3.stl tiedosto mikä voi laittaa suoraan tulostukseen.
    Tulostuksessa käytin prusa one +, PETG ~ 15 min tulostus.
    Toleranssit tossa tulostimessa 0.2mm, joten jos on tarvetta muokata
2026-03-12 Readme jako
    Lisätty selkäsalaman kasaus ohjeet.
2026-03-14 Selkäsalaman readme päivittelyä
    Laitoin nyt oikean kuoret stl tiedoston missä on vain 1 kuori
2026-03-16 Waunujen skemaa muutettu. README tiedostoja päivitetty.
2026-03-27 Kicad projekti tiedostoja siirrelty, selkä rev2 init ja waunujen skema muutosta.
2026-04-10 Lisää putsausta ja selkäsalaman muutosta
2026-06-02 hiomista vaille rev
